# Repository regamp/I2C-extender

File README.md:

# I2C-extender
I2C bus extender, 4 relay output and 4 input
KiCad 9 project

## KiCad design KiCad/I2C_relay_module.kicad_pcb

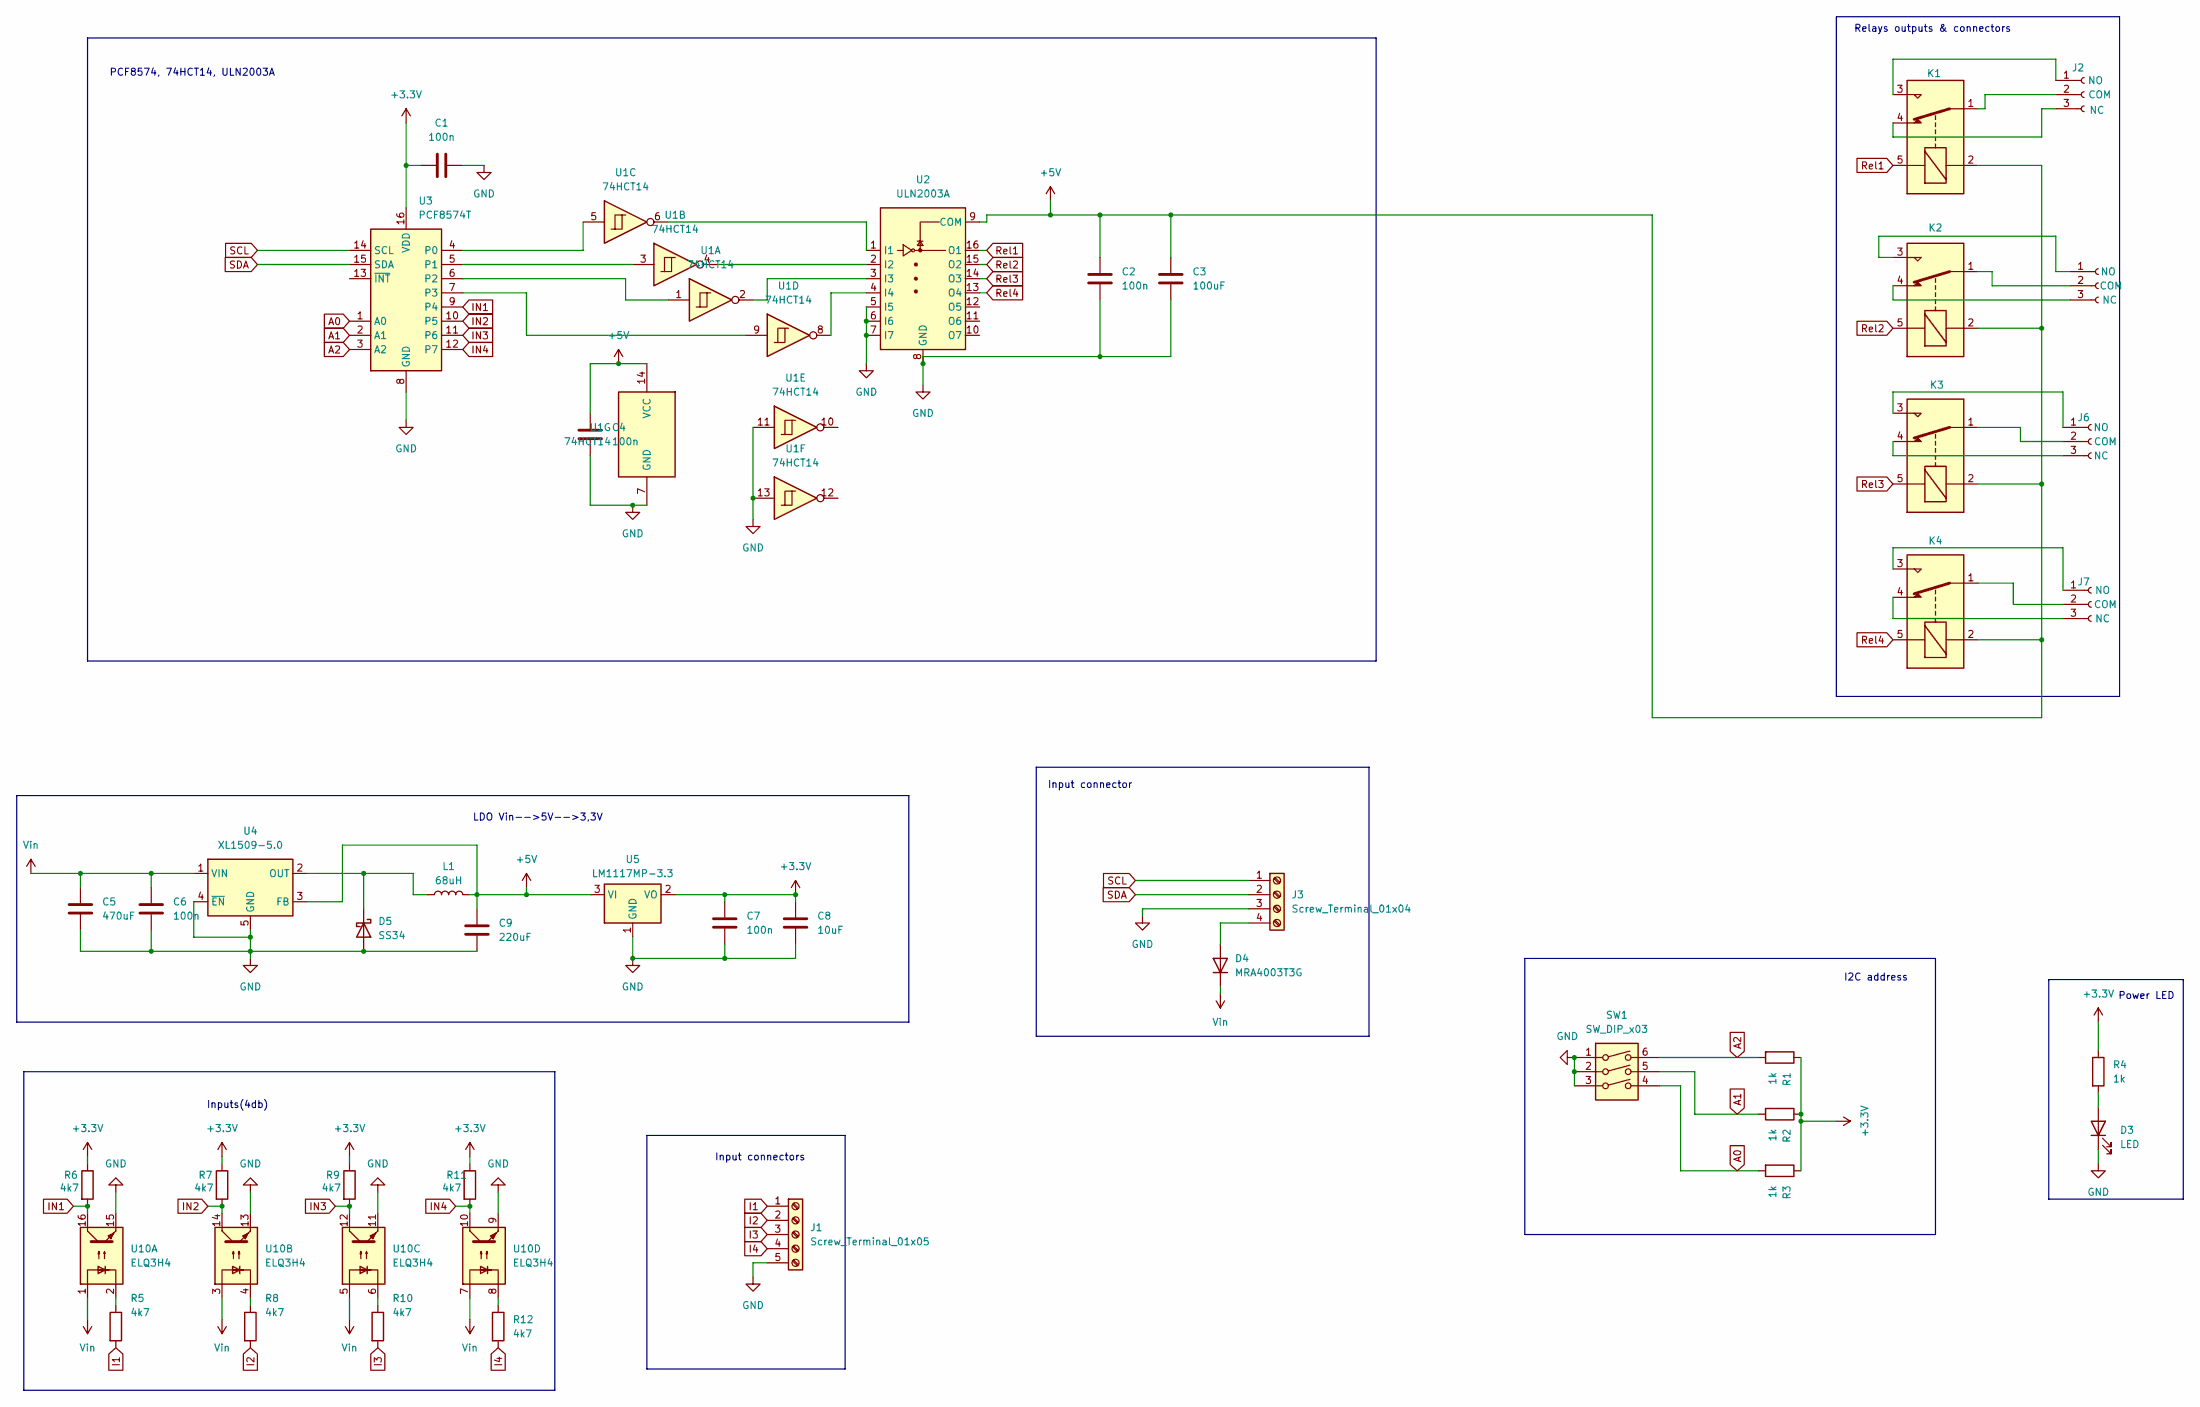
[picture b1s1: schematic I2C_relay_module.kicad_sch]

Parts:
C1, C2, C4, C6, C7: 100n; C_0805_2012Metric_Pad1.18x1.45mm_HandSolder
C3: 100uF; CP_Radial_D5.0mm_P2.50mm
C5: 470uF; C_Radial_D10.0mm_H16.0mm_P5.00mm
C8: 10uF; C_1206_3216Metric_Pad1.33x1.80mm_HandSolder
C9: 220uF; C_Radial_D5.0mm_H11.0mm_P2.00mm
D3: LED; LED_0805_2012Metric_Pad1.15x1.40mm_HandSolder
D4: MRA4003T3G; D_SMA_Handsoldering
D5: SS34; D_SMA_Handsoldering
J1: Screw_Terminal_01x05; TerminalBlock_MetzConnect_Type059_RT06305HBWC_1x05_P3.50mm_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
J2, J5, J6, J7: Conn_01x03_Socket; PhoenixContact_MCV_1,5_3-G-3.5_1x03_P3.50mm_Vertical
J3: Screw_Terminal_01x04; TerminalBlock_MetzConnect_Type059_RT06304HBWC_1x04_P3.50mm_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
K1, K2, K3, K4: SANYOU_SRD_Form_C; Relay_SPDT_SANYOU_SRD_Series_Form_C
L1: 68uH; L_Ferrocore_DLG-0504
R1, R2, R3, R4: 1k; R_0805_2012Metric_Pad1.20x1.40mm_HandSolder
R5, R6, R7, R8, R9, R10, R11, R12: 4k7; R_0805_2012Metric_Pad1.20x1.40mm_HandSolder
SW1: SW_DIP_x03; SW_DIP_SPSTx03_Slide_9.78x9.8mm_W7.62mm_P2.54mm
U1: 74HCT14; SOIC-14_3.9x8.7mm_P1.27mm
U2: ULN2003A; SOIC-16W_5.3x10.2mm_P1.27mm
U3: PCF8574T; SOIC-16W_7.5x10.3mm_P1.27mm
U4: XL1509-5.0; SOIC-8_3.9x4.9mm_P1.27mm
U5: LM1117MP-3.3; SOT-223-3_TabPin2
U10: ELQ3H4; SOP-16_4.4x10.4mm_P1.27mm

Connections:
+3.3V: C1.1, C7.2, C8.1, R1.1, R2.1, R3.1, R4.1, R6.1, R7.1, R9.1, R11.1, U3.16 (VDD), U5.2 (VO)
+5V: C2.1, C3.1, C4.2, C9.1, K1.2, K2.2, K3.2, K4.2, L1.2, U1.14 (VCC), U2.9 (COM), U4.3 (FB), U5.3 (VI)
A0: R3.2, SW1.4, U3.1 (A0)
A1: R2.2, SW1.5, U3.2 (A1)
A2: R1.2, SW1.6, U3.3 (A2)
GND: C1.2, C2.2, C3.2, C4.1, C5.2, C6.1, C7.1, C8.2, C9.2, D3.1 (K), D5.2 (A), J1.5, J3.3, SW1.1, SW1.2, SW1.3, U1.7 (GND), U1.11, U1.13, U2.5 (I5), U2.6 (I6), U2.7 (I7), U2.8 (GND), U3.8 (GND), U4.4 (~EN), U4.5 (GND), U4.6 (GND), U4.7 (GND), U4.8 (GND), U5.1 (GND), U10.9, U10.11, U10.13, U10.15
I1: J1.1, R5.2
I2: J1.2, R8.2
I3: J1.3, R10.2
I4: J1.4, R12.2
IN1: R6.2, U3.9 (P4), U10.16
IN2: R7.2, U3.10 (P5), U10.14
IN3: R9.2, U3.11 (P6), U10.12
IN4: R11.2, U3.12 (P7), U10.10
unnamed: D3.2 (A), R4.2
unnamed: D4.2 (A), J3.4
unnamed: D5.1 (K), L1.1, U4.2 (OUT)
unnamed: J2.1, K1.3
unnamed: J2.2, K1.1
unnamed: J2.3, K1.4
unnamed: J5.1, K2.3
unnamed: J5.2, K2.1
unnamed: J5.3, K2.4
unnamed: J6.1, K3.3
unnamed: J6.2, K3.1
unnamed: J6.3, K3.4
unnamed: J7.1, K4.3
unnamed: J7.2, K4.1
unnamed: J7.3, K4.4
unnamed: R5.1, U10.2
unnamed: R8.1, U10.4
unnamed: R10.1, U10.6
unnamed: R12.1, U10.8
unnamed: U1.6, U2.1 (I1)
unnamed: U1.4, U2.2 (I2)
unnamed: U1.2, U2.3 (I3)
unnamed: U1.8, U2.4 (I4)
unnamed: U1.5, U3.4 (P0)
unnamed: U1.3, U3.5 (P1)
unnamed: U1.1, U3.6 (P2)
unnamed: U1.9, U3.7 (P3)
Rel1: K1.5, U2.16 (O1)
Rel2: K2.5, U2.15 (O2)
Rel3: K3.5, U2.14 (O3)
Rel4: K4.5, U2.13 (O4)
SCL: J3.1, U3.14 (SCL)
SDA: J3.2, U3.15 (SDA)
Vin: C5.1, C6.2, D4.1 (K), U4.1 (VIN), U10.1, U10.3, U10.5, U10.7

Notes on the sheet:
Input connectors
Power LED
I2C address
Input connector
Inputs(4db)
Relays outputs & connectors
PCF8574, 74HCT14, ULN2003A
LDO Vin-->5V-->3,3V

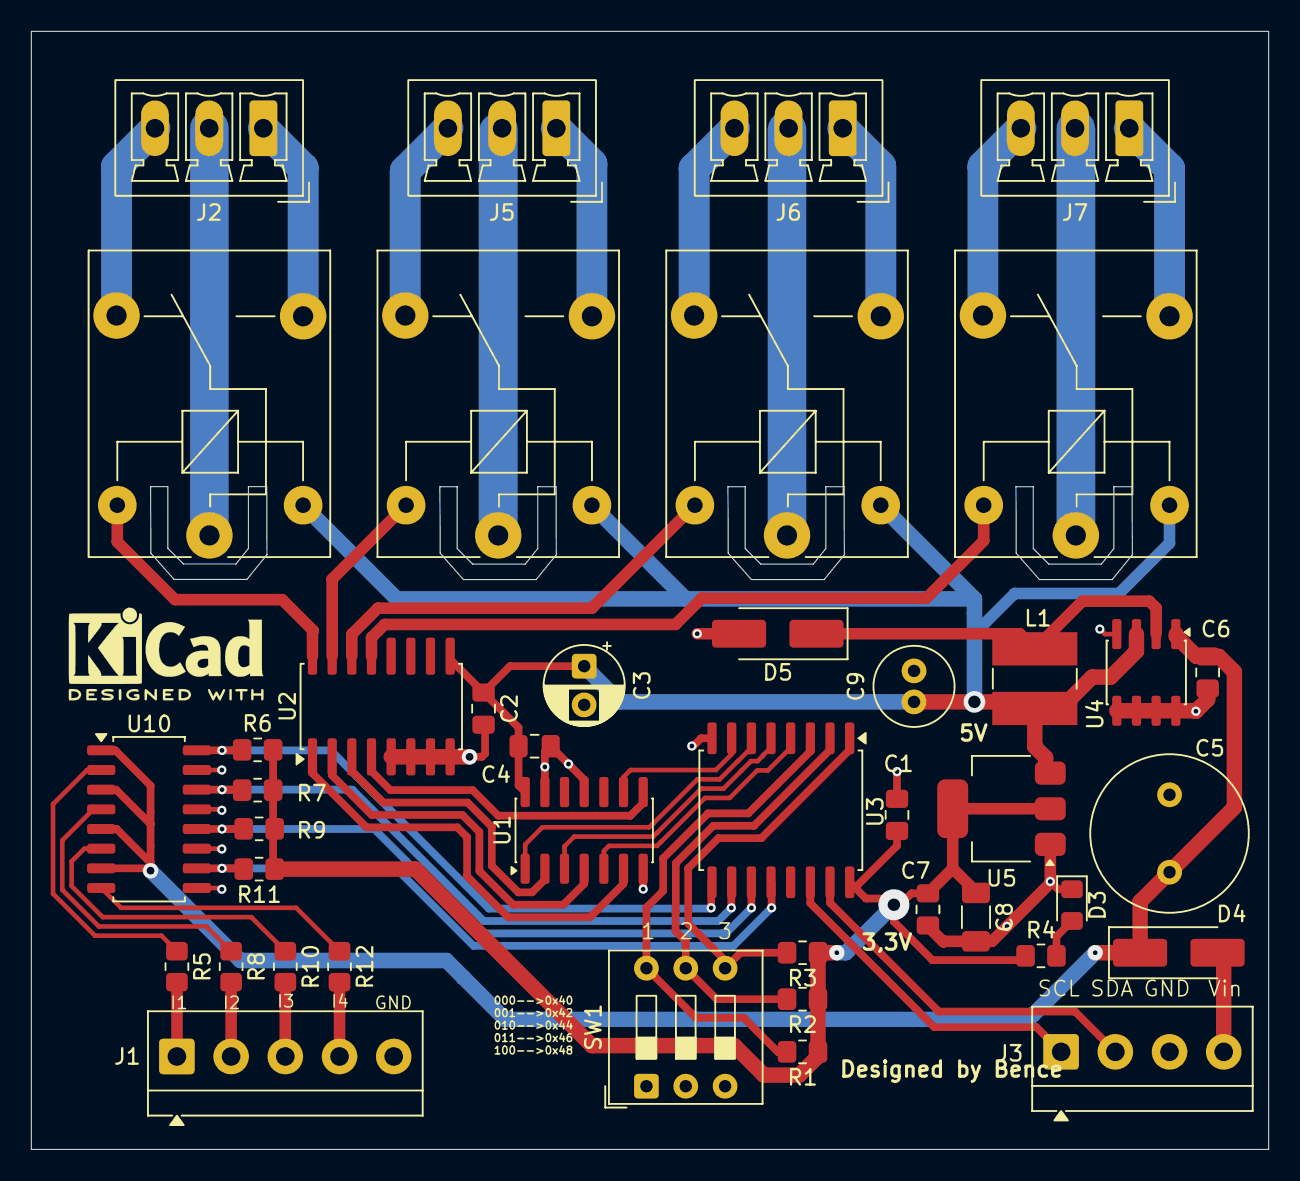
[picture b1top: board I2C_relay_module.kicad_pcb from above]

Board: 2 copper layers, 79.9 x 72.2 mm, 42 parts (0 on the bottom side), 48 nets.

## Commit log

2026-02-03 Add KiCad 9 project mention to README
2026-02-03 Add images to README for better visualization
    Added images to enhance project documentation.
2026-02-03 Add GNU General Public License v3
    Added the GNU General Public License version 3 to the project.
2026-02-03 Create Picture
2026-02-03 Add file.txt with initial content
2026-02-03 Add se.txt file
2026-02-03 Rename I2C_relay_module.kicad_pcb to KiCad/I2C_relay_module.kicad_pcb
2026-02-03 Rename I2C_relay_module.kicad_prl to KiCad/I2C_relay_module.kicad_prl
2026-02-03 Rename I2C_relay_module.kicad_pro to KiCad/I2C_relay_module.kicad_pro
2026-02-03 Rename I2C_relay_module.kicad_sch to KiCad/I2C_relay_module.kicad_sch
2026-02-03 Rename ezgif.com-animated-gif-maker.gif to GIF.gif
